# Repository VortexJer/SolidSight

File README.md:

# AISight

**Sight for AI agents.** An agent cannot look at a screen — and almost
everything creative software asks a human to *look at* is actually a
measurable property of the data. AISight is a family of five
independent tools, one per domain, that replace looking with measuring:
deterministic builds, exact reports with `where` and `try:` on every
finding, and renders only as evidence for what the numbers found.

| tool | domain | replaces | docs |
|---|---|---|---|
| **solidsight** | 3D design / CAD / 3D printing | eyes on a viewport | [README](solidsight/README.md) |
| **animationsight** | animation clips, mocap (.bvh) | watching the take | [README](animationsight/README.md) |
| **texturesight** | UVs + texture maps | squinting at a checker | [README](texturesight/README.md) |
| **shadersight** | materials/BRDFs + node graphs | rendering a sphere | [README](shadersight/README.md) |
| **pcbsight** | PCB layouts (.kicad_pcb) | eyeballing copper | [README](pcbsight/README.md) |

## Install

Each tool is its own pip package: install **one**, **some**, or **all**.
They share a philosophy, not a dependency — none requires another.

**One tool**, from PyPI:

```bash
pip install solidsight
pip install animationsight
pip install texturesight
pip install shadersight
pip install pcbsight
```

**All five** in one line — `aisight` depends on every tool, so it pulls
the family in, and is also the command that takes it back off:

```bash
pip install aisight
```

**The unreleased `main`**, or a checkout you are editing:

```bash
pip install "git+https://github.com/VortexJer/AISight#subdirectory=solidsight"
# or
git clone https://github.com/VortexJer/AISight && pip install ./AISight/solidsight
```

Requirements: Python >= 3.10, pip, git. solidsight carries the heavy
dependencies (manifold3d, trimesh, scipy, matplotlib — all wheels); the
other four need only numpy and pillow.

### As a Claude Code plugin

The same five tools are also a plugin marketplace. In Claude Code:

```
/plugin marketplace add VortexJer/AISight
/plugin install solidsight@aisight
```

The plugin carries the skill; the skill still needs the CLI it drives,
so `pip install solidsight` as well. Installing the pip package alone is
enough — it self-installs its skill (see below); the plugin route exists
for people who manage their agent's capabilities through `/plugin`.

## Uninstalling

```bash
aisight status          # what is installed on this machine
aisight uninstall       # every skill, every package, the marketplace
```

It removes the five skills from `~/.claude/skills/`, pip-uninstalls the
packages, drops the `aisight` marketplace from
`~/.claude/plugins/marketplaces/` and its registry entry — and then
itself, last. `--only <tool>` limits it to one tool, `--dry-run` prints
the list without touching anything, `--keep-packages` keeps pip.

A git checkout is yours, not ours, so it is never guessed:
`--repo PATH` deletes one, and only after checking the directory really
is an AISight working copy. Each tool also keeps its own
`<tool> uninstall` (that tool's skill + package). Details:
[aisight/README.md](aisight/README.md).

## What installing gives an AI agent

Every tool ships its **Claude Code skill inside the pip package**. The
first time its CLI runs on a machine that has Claude Code (`~/.claude`
exists), the skill installs itself into `~/.claude/skills/<tool>/` and
keeps itself updated on version changes — from then on, any new agent
session routes matching requests to the tool ("design a bracket" ->
solidsight, "review this .bvh" -> animationsight, "check my board" ->
pcbsight). No Claude Code? The CLIs work standalone for humans and
scripts; nothing else is touched.

`<tool> uninstall` removes that tool's skill and package; `aisight
uninstall` removes all of it at once (above). No telemetry, no services,
no accounts.

## The showcase: one robot through all five tools

[`showcase/`](showcase/) takes **Vigía**, a desk robot, from nothing to
a printable enclosure, a routed controller board, a simulation-ready
URDF, a textured game asset, validated materials and a reviewed servo
gesture — entirely by an AI agent, entirely through measurements. The
enclosure does not copy the board's dimensions: it **imports pcbsight
and reads them from the .kicad_pcb**, so the standoffs sit at the
board's own mounting pads.

Every stage caught real defects the agent could not see — 31 board
findings (both USB nets open with swapped ends), five enclosure
iterations (servos placed where the servo *headers* are, a neck ring
floating over the open shell), a flipped UV island, a boosted copper
emitting 53% more light than it receives, a stepped servo profile demanding 3600 deg/s of a 600 deg/s servo —
and every fix ends in a diff that proves it.

<p align="center"><em>the assembly with its electronics as X-ray ghosts · the board pcbsight took from 31 findings to 0 · the boosted-vs-physical copper · the robot performing its servo gesture</em></p>

Full narrative and the defect scoreboard: [showcase/README.md](showcase/README.md).

## Blind vs measured: the controlled studies

Five hero examples run the same experiment: a cold-context agent with
**no tools at all** (numpy/PIL/trimesh, no viewer, one shot) attempts a
hard commission; the same commission then goes through the tool's loop.
The blind sides are genuinely competent — the defects they ship are the
ones nobody can see without measuring:

| study | blind | after |
|---|---|---|
| [engine block](docs/comparison) (solidsight) | 8 sealed water-jacket pockets (two of 37 cm³), cap bolts 1.9 mm from the crank tunnel, oil gallery 3 mm from coolant | the loop caught the author's own 4 equivalent mistakes, each fixed to a measured wall |
| [parkour vault](animationsight/examples/03-parkour) (animationsight) | a 0.47x g stride, root on rails in the turn, a knee pop at landing | **OK — 0 findings**, every flight at 1 g |
| [hero crate](texturesight/examples/03-crate-hero) (texturesight) | 148 flipped UVs (FAIL), 7.35:1 stretch, 54x density spread | 0 flips, 1.005 anisotropy, 3.35x |
| [material set](shadersight/examples/04-materials) (shadersight) | 8/8 conserve — the one FAIL was the tool's own estimator noise | tool fixed + graph 436 → 204 ALU/px |
| [rover board](pcbsight/examples/02-rover) (pcbsight) | 12 open nets, 26 clearance faults | routed: **OK — 0 findings** |

**Left: blind. Right: through the loop.** Same commission, same author
competence — the only variable is being able to measure.

<p align="center"><em>the inline-4 engine — blind: watertight, single shell, shipped convinced of success; the audit then found <b>eight sealed water-jacket pockets</b> no coolant can ever reach, cap-bolt drillings 1.9 mm from the crank tunnel, and the 2 mm sliver the author itself predicted it might leave · through the loop: the author made the same kinds of mistakes — the loop caught all four</em></p>

<p align="center"><em>the parkour vault — blind: a 0.47x g stride, a turn step on invisible rails, a knee pop at the landing · after: every flight at 1 g, <b>0 findings</b></em></p>

<p align="center"><em>how to read a UV picture: the flat shapes ARE the crate's surface peeled onto the texture (same colour = same piece — a box unfolded into its cardboard template)</em></p>

<p align="center"><em>the hero crate's UVs — blind: 148 flipped faces (red), 7.35:1 stretch, 336 stacked islands · after: same geometry and maps, mapper rewritten — 0 flips, welded shells, 92% packing</em></p>

<p align="center"><em>what shadersight is for: the "boosted highlights" copper emits <b>1.7x the light it receives</b> (curve far above the red ceiling) yet its preview sphere looks almost identical to the physical one — the eye can't audit energy. The blind-vs-measured study's twist: the blind author knew its F0s and <b>refused the boost bait</b>; the one FAIL was the tool's own estimator noise on an exact-F0 gold, fixed at 16x sampling.</em></p>

<p align="center"><em>the rover board — blind: 12 open nets, 26 clearance faults circled in red · after: routed, <b>0 findings</b></em></p>

Each README credits what the blind side got right, ties every fix to a
measured finding, and lists the bugs the studies forced back into the
tools themselves.

## The standard every tool holds itself to

- **Known ground truth**: every example is synthetic on purpose, with
  defects injected at exact magnitudes, so the tests assert the *right*
  answer — and that the clean reference stays clean, because false
  positives are how a tool loses the right to be believed.
- **Deterministic**: same input, byte-identical report; fixed seeds
  where sampling is involved, resolution stated in the report.
- **The full loop**: inspect -> fix -> **diff to prove the fix did what
  you meant and nothing else**.
- **Honest scope**: each README lists what is NOT read or checked.

The family overview — and the bugs each tool caught in its own
reference, which is the recurring proof of the whole idea:
[docs/roadmap-sights.md](docs/roadmap-sights.md).

## Repository layout

```
solidsight/      3D design: engine + CLI, skills/ (+ domains/), examples, benchmarks
animationsight/  motion clips as measurement
texturesight/    UVs + texture maps
shadersight/     materials + node graphs
pcbsight/        board layouts
aisight/         the family command: status + one clean uninstall
showcase/        Vigia: one robot through all five tools (the flagship demo)
docs/            the blind-vs-loop comparison study, plugins, family roadmap
```

Each tool folder is self-contained: `pyproject.toml`, the package, its
`skills/<tool>/`, `examples/` with committed real outputs, and
`tests/`.

## License

MIT

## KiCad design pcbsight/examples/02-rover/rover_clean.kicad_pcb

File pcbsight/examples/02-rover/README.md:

# 02 — A 4-motor rover controller (blind vs the loop)

The complex example: a real rover board — MCU (RP2040), IMU
(MPU6050), four motor connectors, a battery entry, a USB-C data pair,
a status LED, three decoupling caps — **14 nets, 13 components**. Built
twice, the way solidsight's engine block is:

- **`rover_blind.kicad_pcb`** is routed the way a fresh agent would with
  only the netlist and no way to SEE the copper: short diagonals laid
  between pads it cannot tell are in the way. It ships the defects that
  come *from* being blind.
- **`rover_clean.kicad_pcb`** is the same board taken to **zero
  findings** — routed by a real 2-layer maze router that reads each
  pad's actual position from pcbsight and keeps a clearance halo around
  everything it lays down.

```bash
python make_rover.py
pcbsight inspect rover_blind.kicad_pcb   # FAILED
pcbsight inspect rover_clean.kicad_pcb   # OK
pcbsight diff rover_blind.kicad_pcb rover_clean.kicad_pcb
```

## Before (blind) vs after (the loop)

<p align="center"><em>left: routed blind — diagonals crossing pads, findings circled in red, three motors and the IMU never reached. right: a clean 2-layer route, every net closed. Same components, same nets.</em></p>

The blind board is not a strawman — it is exactly what routing without
sight produces: **12 of 14 nets left open, 26 clearance violations**,
the USB pair swapped and unmatched, the battery rail necked to 0.25 mm.
None of it is visible as "wrong" without measuring the copper.

## The diff tells the whole repair

```
pcbsight diff rover_blind.kicad_pcb rover_clean.kicad_pcb
  tracks: 12 -> 113          vias: 0 -> 27
  net 'GND':    6 island(s) -> 1
  net 'USB_DP': 4 island(s) -> 1
  net 'USB_DM': 4 island(s) -> 1
  net 'M2_A' .. 'M4_B':      2 island(s) -> 1   (each motor pair reached)
  clearance findings: 26 -> 0
  ... every net-open and clearance finding GONE
```

## Why the render looks like a board

Every component carries its silkscreen body, reference (U1, J2, D1...)
and value (RP2040, MOTOR, LED...); the substrate is the real Edge.Cuts
outline; gold is the front copper, dim gold the back. That is the point
of the render overhaul — a PCB review has to *look* like a PCB, or the
findings float in the void.

The clean side is genuinely routed, not decorated: `_router.py` is a
small Lee/BFS maze router (two layers, vias, a clearance halo) so the
"after" is a board that actually connects — the same standard the
family holds everywhere: the fixed reference must really be fixed.

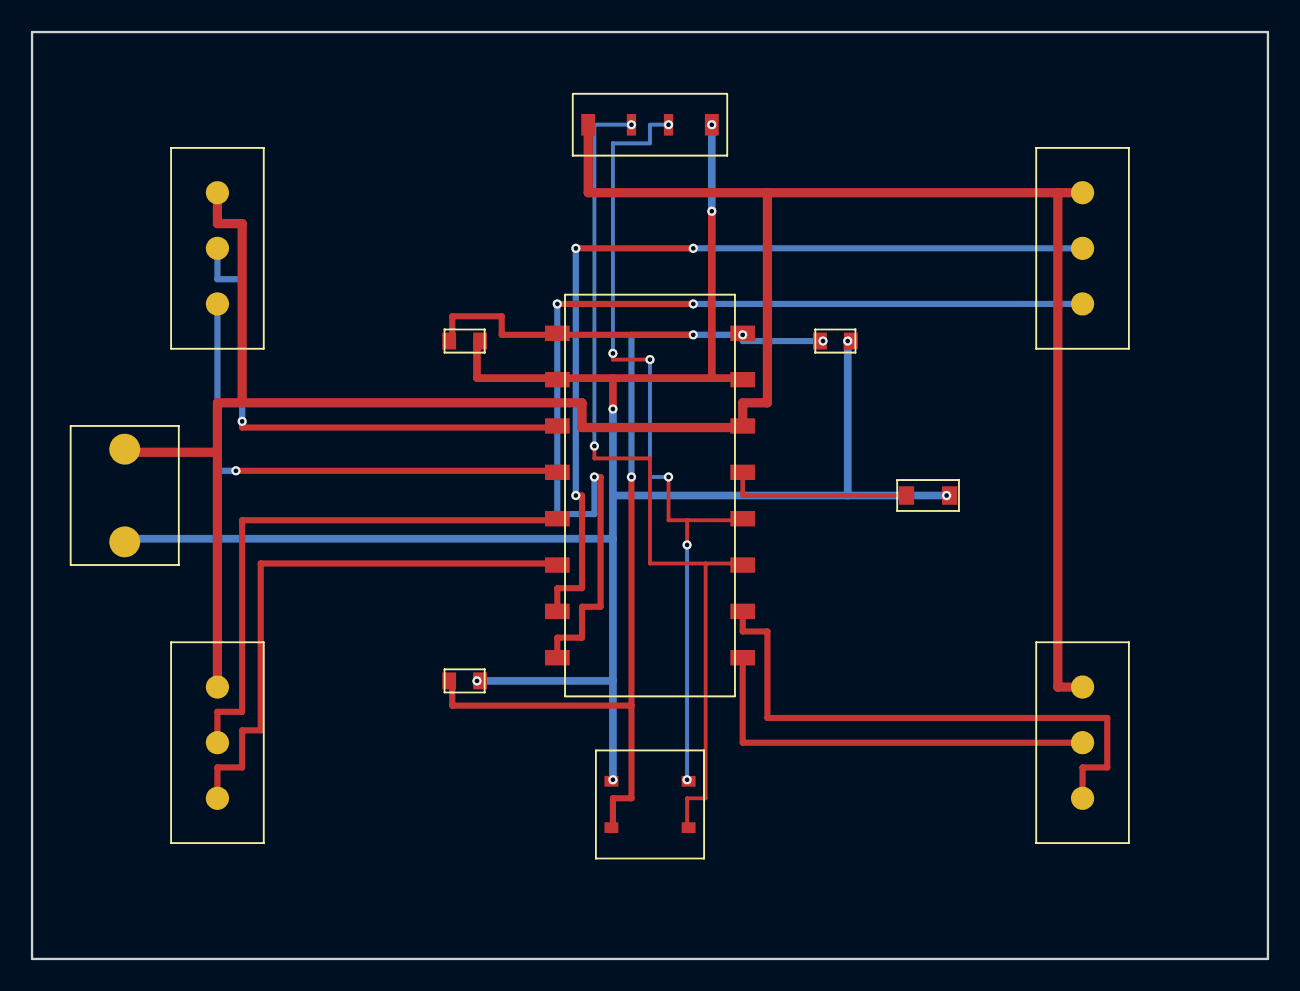
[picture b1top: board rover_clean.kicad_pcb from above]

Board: 0 copper layers, 80.0 x 60.0 mm, 12 parts (0 on the bottom side), 14 nets.

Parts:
C1: 100n; C1
C2: 100n; C2
C3: 100n; C3
D1: LED; D1
J1: BATT; J1
J2: MOTOR; J2
J3: MOTOR; J3
J4: MOTOR; J4
J5: MOTOR; J5
J6: USB-C; J6
U1: RP2040; U1
U2: MPU6050; U2

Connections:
+3V3: C1.1, C2.1, C3.1, U1.1, U1.16, U2.1
GND: C1.2, C2.2, C3.2, D1.2, J1.2, J6.4, U1.2, U1.15, U2.2
LED: D1.1, U1.13
M1_A: J2.2, U1.3
M1_B: J2.3, U1.4
M2_A: J3.2, U1.5
M2_B: J3.3, U1.6
M3_A: J4.2, U1.7
M3_B: J4.3, U1.8
M4_A: J5.2, U1.9
M4_B: J5.3, U1.10
USB_DM: J6.2, U1.12, U2.4
USB_DP: J6.1, U1.11, U2.3
VBAT: J1.1, J2.1, J3.1, J4.1, J5.1, J6.3, U1.14

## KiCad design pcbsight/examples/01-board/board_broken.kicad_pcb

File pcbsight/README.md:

# pcbsight

**PCB review built exclusively for AI agents.** A `.kicad_pcb` in;
exact connectivity, clearance, current and pair findings out, with
coordinates.

A layout is judged by eyeballing the copper. But an open net is a
union-find question over copper that actually touches, a clearance is a
segment-to-segment distance minus the widths, current capacity is
IPC-2221 arithmetic at the net's narrowest point, and differential-pair
skew is a subtraction. None of it needs eyes.

```bash
pip install pcbsight

pcbsight inspect board.kicad_pcb --clearance 0.15
# -> [FAIL] net 'GND' is 2 separate island(s) - unconnected pad(s): J1.2
# -> [FAIL] track-track: '+5V' to 'SIG' at 0.08 mm (required 0.15)
#           where: F.Cu near (28.75, 16.37)
# -> current: '+5V' min width 0.2 mm -> 0.746 A at dT=10 C (external)
# -> pair: USB_P / USB_N - skew 3.0 mm (~19.8 ps on FR4)
# -> out/board.png   (copper as drawn, findings circled in red)

pcbsight impedance 0.3 0.2      # ~51 ohm microstrip (IPC-2141 estimate)
```

Or as a Claude Code plugin:

```
/plugin marketplace add VortexJer/AISight
/plugin install pcbsight@aisight
```

(the plugin carries the skill; the CLI it drives still comes from pip)

Exit codes: 0 ok, 1 bad input, 2 a FAIL-level finding. Deterministic.

## What it measures

| | |
|---|---|
| **connectivity** | union-find over copper that geometrically touches (tracks by width, vias across layers, pads by extent): islands per net, the unconnected pads named |
| **clearance** | exact segment distances minus copper widths, per layer, different nets only; FAIL below 50 % of the rule (etch-short territory), warn above |
| **current** | IPC-2221 external/internal curve at the net's *narrowest* track, with copper weight and dT stated |
| **diff pairs** | found by net name (`_P/_N`, `+/-`, deduped); width match and length skew in mm and ~ps |
| **impedance** | IPC-2141 microstrip estimate, labelled an estimate |

Footprint pads are composed through the footprint's placement —
rotation included, because a pad's `(at ...)` is local and skipping the
rotation silently misplaces every pad of every rotated footprint
(`test_rotated_footprint_pads_are_composed`).

## Proof it works: known ground truth

`examples/01-board` is a small 2-layer board generated twice: clean, and
with four defects injected at exact magnitudes.

| injected | measured |
|---|---|
| GND bottom trace stops 18.5 mm short of J1 | `[FAIL] net 'GND' is 2 separate island(s) ... unconnected pad(s): J1.2` |
| SIG routed 0.08 mm from +5V | clearance **0.08 mm** (exact), coordinates given |
| +5V necked to 0.2 mm | `min width 0.2 mm -> 0.746 A` (the 1.0 mm run: 2.39 A, on the published IPC curve) |
| USB pair: one side +3 mm detour, width 0.25 vs 0.3 | skew **3.0 mm** (~19.8 ps), `width_matched: false` |

The clean board reports **OK, exit 0, zero findings** — asserted in the
tests, both directions.

<p align="center"><em>the broken board: the neck in the top trace, the blue GND run stopping short, the 0.08 mm findings circled</em></p>

## The complex example: a 4-motor rover controller

[`examples/02-rover`](examples/02-rover) is the full thing — MCU, IMU,
four motor connectors, battery, USB-C, LED, decoupling: **14 nets, 13
components**, built blind (netlist only, no sight of the copper) against
the same board taken to zero findings by a real 2-layer maze router.

<p align="center"><em>routed blind (12 of 14 nets open, 26 clearance violations, findings circled) vs the clean 2-layer route — same components, same nets</em></p>

```
pcbsight diff rover_blind.kicad_pcb rover_clean.kicad_pcb
  tracks: 12 -> 113   vias: 0 -> 27
  net 'GND': 6 island(s) -> 1 ... every motor pair reached
  clearance findings: 26 -> 0
```

## The intro example: before / after in miniature

The repair of the broken board, told entirely by `diff` — no
re-inspection choreography, one command against both files:

```
pcbsight diff board_broken.kicad_pcb board_clean.kicad_pcb
  net 'GND': 2 island(s) -> 1
  clearance findings: 2 -> 0
  current '+5V': 0.745 A -> 2.392 A (min width 0.2 -> 1.0 mm)
  pair USB_P / USB_N: skew 3.0 -> 0.0 mm
  GONE [net-open]        net 'GND' is 2 separate island(s) ... unconnected pad(s): J1.2
  GONE [clearance]       track-track: '+5V' to 'SIG' at 0.08 mm (required 0.2)
  GONE [diff-pair-skew]  pair USB_P / USB_N is skewed 3.0 mm (~19.8 ps on FR4)
  GONE [diff-pair-width] pair USB_P / USB_N mixes widths [0.25, 0.3] mm
```

<p align="center"><em>before: the GND run (blue) stops short, the neck in the +5V trace, the 0.08 mm findings circled · after: routed, clean, matched</em></p>

## Two of its own defects the example caught

1. The first "clean" board routed +5V straight through the GND and SIG
   pads — pcbsight flagged its own reference at 0.0 mm clearance. The
   example was wrong; the check was not. It stays in the generator as a
   comment.
2. `USB_P/USB_N` matched two suffix rules (`_P/_N` and `P/N`) and was
   reported twice. Pairs are now deduped by the net pair, and the test
   asserts exactly one.

## Honest limitations

- **Zones/pours are not read**: a net routed only through a copper pour
  will read as open here. Where pours carry nets, confirm in KiCad's
  own DRC — this tool complements it, it does not replace it.
- Current numbers assume a lone trace in still air (that is what
  IPC-2221 tabulates); planes and vias change the real number.
- The impedance estimate is IPC-2141 (~10 %); controlled impedance
  needs the fab's field-solved stackup.
- Arcs, curved traces, keepouts and mask/paste layers are not parsed.

Siblings, same philosophy: [solidsight](../solidsight/README.md) (geometry — export
the board outline there to check the enclosure fit),
[animationsight](../animationsight/README.md),
[texturesight](../texturesight/README.md),
[shadersight](../shadersight/README.md).

Leaving: `pcbsight uninstall` removes this tool's skill and package.
`pip install aisight && aisight uninstall` removes the whole family —
every skill, every package and the plugin marketplace. See
[aisight](../aisight/README.md).

## License

MIT

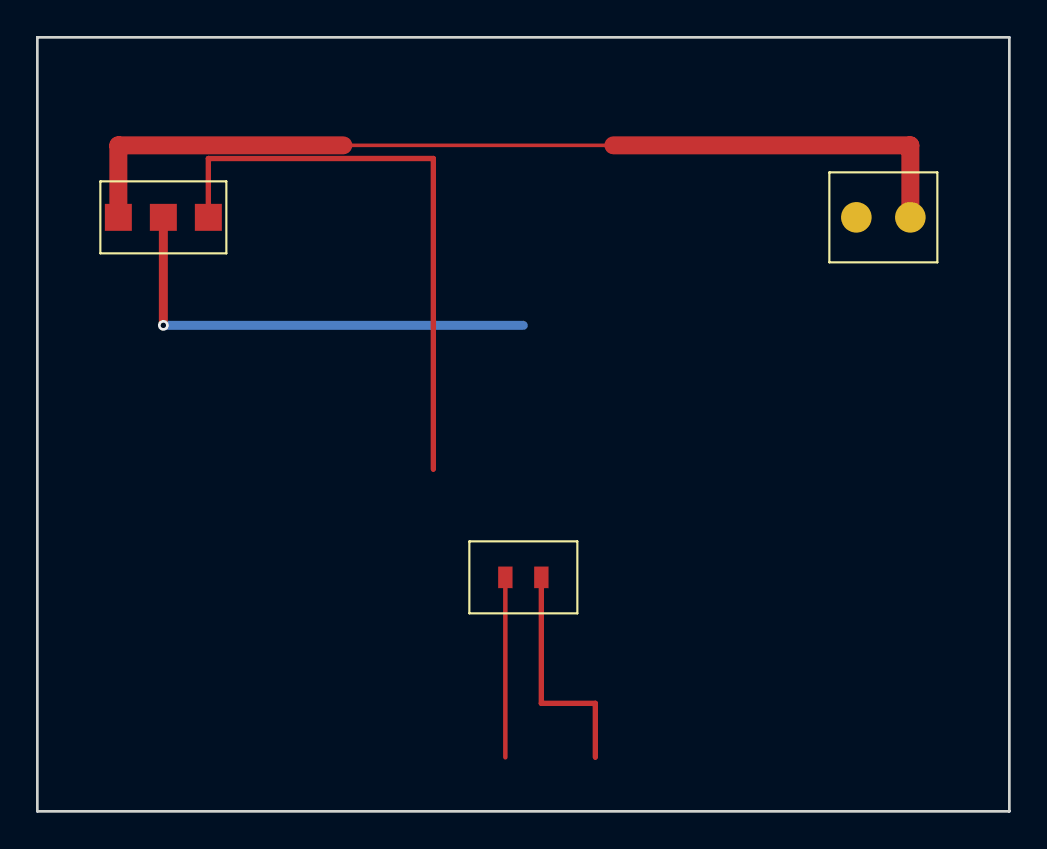
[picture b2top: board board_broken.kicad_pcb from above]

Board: 0 copper layers, 54.0 x 43.0 mm, 3 parts (0 on the bottom side), 2 nets.

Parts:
J1: PWR; J1
J2: USB; J2
U1: AP2112; U1

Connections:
+5V: J1.1, U1.1
GND: J1.2, U1.2
